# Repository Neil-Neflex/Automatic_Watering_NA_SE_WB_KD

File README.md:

Ce dépôt est organisé de manière à séparer la documentation de conception du code source technique. Pour naviguer efficacement, le projet utilise deux branches distinctes.

## Organisation des branches

- **Branche main**: Centralise la documentation, les rapports de projet et les études d'impact.
- **Branche partie-logicielle**: Contient exclusivement le code source et les fichiers de configuration.

## Contenu de la branche Main

- **DOCS**: Ressources techniques et rapports des membres du groupe par séance.
- **ecoconception**: Analyse du cycle de vie et choix techniques pour minimiser l'empreinte énergétique.
- **Hardware-pcb-eagle**: Schémas électroniques et fichiers PCB réalisés sous Eagle.
- **ProjetS7.pdf**: Présentation S8.
- **RAPPORT.pdf**: Rapport de synthèse présentant les objectifs et résultats du semestre 7 et 8.

## Architecture logicielle

Le code est segmenté par modules fonctionnels(exemple) :
- **Watering_System.ino**: Point d'entrée principal du programme.
- **SensorManagment (.cpp/.h)**: Logique de traitement des capteurs.
- **VanneCase (.h)**: Gestion des états de l'électrovanne.
- **ModuleHorloge (.cpp/.h)**: Gestion du temps réel (RTC).

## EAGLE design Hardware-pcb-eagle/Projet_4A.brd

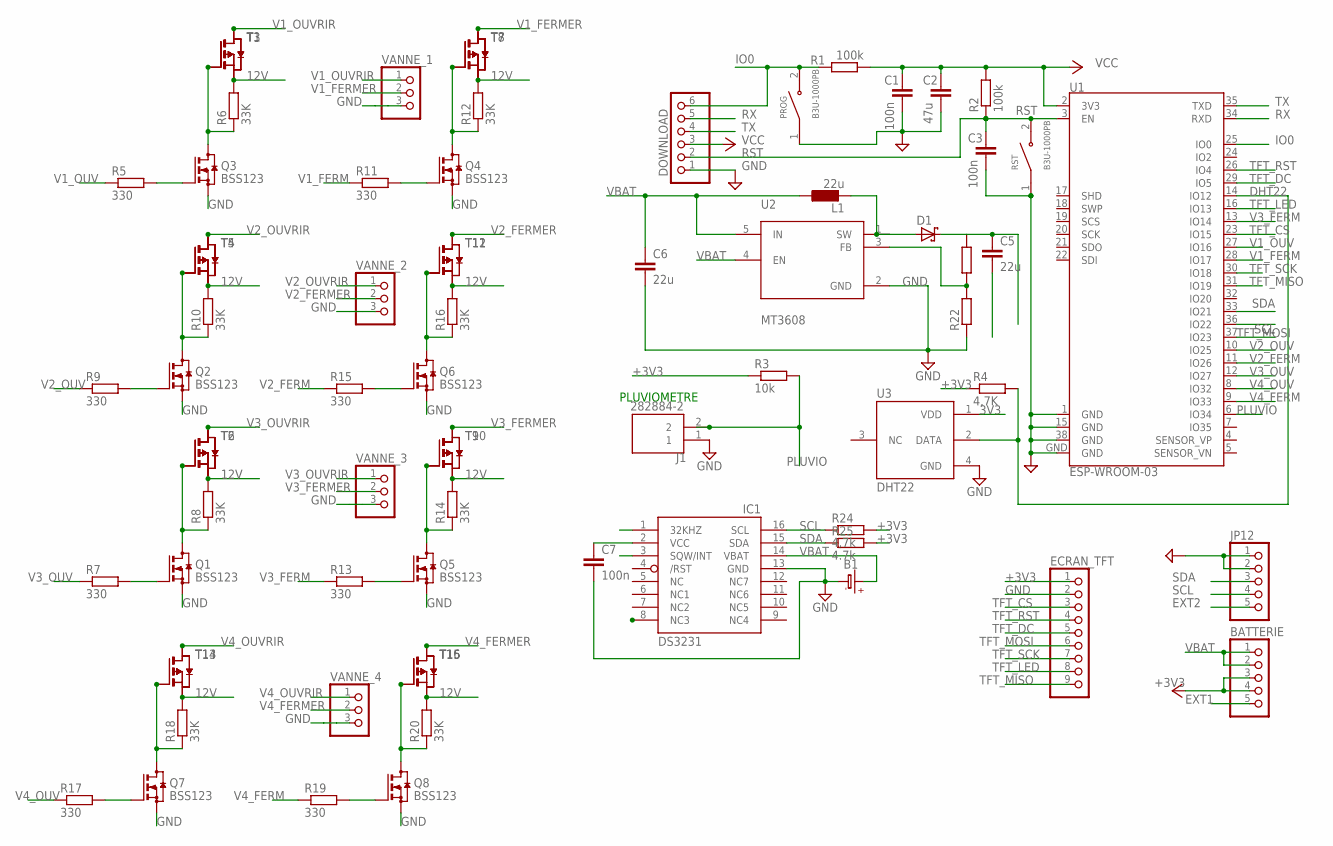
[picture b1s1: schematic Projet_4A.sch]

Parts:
B1: BATTERYCR2032_BAT-HLD-001; CR2032_SMT_BAT-HLD-001
BATTERIE: PINHD-1X5S; 1X05S
C1, C3, C7: 100n; C0805
C2: 47u; C0805
C5, C6: 22u; C0805
D1: SCHOTTKY-DIODEAG; AG
DOWNLOAD: PINHD-1X6S; 1X06S
ECRAN_TFT: PINHD-1X9; 1X09
IC1: DS3231/SO; SO16W
J1: 282884-2; TE_282884-2
JP12: PINHD-1X5S; 1X05S
L1: 22u; 0204/7
PROG: B3U-1000PB; SW_B3U-1000PB
Q1, Q2, Q3, Q4, Q5, Q6, Q7, Q8: BSS123; SOT23
R1, R2: 100k; R1206
R3: 10k; R0805
R4: 4,7K; 0207/10
R5, R7, R9, R11, R13, R15, R17, R19: 330; 0207/10
R6, R8, R10, R12, R14, R16, R18, R20: 33K; 0207/10
R22: R-EU_0204/2V; 0204V
R24: 4,7k; 0204V
R25: 4.7k; 0204V
RST: B3U-1000PB; SW_B3U-1000PB
T1, T2, T3, T4, T5, T6, T7, T8, T9, T10, T11, T12, T13, T14, T15, T16: PMOSSOT23; SOT-23
U1: ESP-WROOM-03
U2: MT3608; SOT95P280X145-6N
U3: DHT22; XDCR_DHT22
VANNE_1, VANNE_2, VANNE_3, VANNE_4: PINHD-1X3; 1X03

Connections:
3V3: U3.1 (VDD)
12V: C5.1, D1.C, R6.2, R8.2, R10.2, R12.2, R14.2, R16.2, R18.2, R20.2, T1.2 (S), T2.2 (S), T3.2 (S), T4.2 (S), T5.2 (S), T6.2 (S), T7.2 (S), T8.2 (S), T9.2 (S), T10.2 (S), T11.2 (S), T12.2 (S), T13.2 (S), T14.2 (S), T15.2 (S), T16.2 (S)
+3V3: BATTERIE.3, BATTERIE.4, C7.1, ECRAN_TFT.1, IC1.2 (VCC), R3.1, R4.1, R24.2, R25.2
+12V: Q3.3 (D), R6.1, T1.3 (G), T3.3 (G)
+12V1: Q2.3 (D), R10.1, T4.3 (G), T5.3 (G)
+12V2: Q1.3 (D), R8.1, T2.3 (G), T6.3 (G)
+12V3: Q4.3 (D), R12.1, T7.3 (G), T8.3 (G)
+12V4: Q5.3 (D), R14.1, T9.3 (G), T10.3 (G)
+12V5: Q6.3 (D), R16.1, T11.3 (G), T12.3 (G)
+12V6: Q7.3 (D), R18.1, T13.3 (G), T14.3 (G)
+12V7: Q8.3 (D), R20.1, T15.3 (G), T16.3 (G)
DHT22: R4.2, U1.14 (IO12), U3.2 (DATA)
EXT1: BATTERIE.5
EXT2: JP12.5
GND: B1.-, C1.2, C2.2, C3.2, C6.2, C7.2, DOWNLOAD.1, ECRAN_TFT.2, IC1.13 (GND), J1.1, JP12.1, JP12.2, PROG.1, Q1.2 (S), Q2.2 (S), Q3.2 (S), Q4.2 (S), Q5.2 (S), Q6.2 (S), Q7.2 (S), Q8.2 (S), R22.1, RST.1, U1.1 (GND), U1.15 (GND), U1.38 (GND), U1.GND, U2.2 (GND), U3.4 (GND), VANNE_1.3, VANNE_2.3, VANNE_3.3, VANNE_4.3
GND1: C5.2
IO0: DOWNLOAD.6, PROG.2, R1.2, U1.25 (IO0)
unnamed: Q3.1 (G), R5.2
unnamed: Q2.1 (G), R9.2
unnamed: Q1.1 (G), R7.2
unnamed: Q4.1 (G), R11.2
unnamed: Q5.1 (G), R13.2
unnamed: Q6.1 (G), R15.2
unnamed: Q7.1 (G), R17.2
unnamed: Q8.1 (G), R19.2
unnamed: D1.A, L1.2, U2.1 (SW)
unnamed: R22.2, U2.3 (FB)
PLUVIO: J1.2, R3.2, U1.6 (IO34)
RST: C3.1, DOWNLOAD.2, R2.1, RST.2, U1.3 (EN)
RX: DOWNLOAD.5, U1.34 (RXD)
SCL: IC1.16 (SCL), JP12.4, R24.1, U1.36 (IO22)
SDA: IC1.15 (SDA), JP12.3, R25.1, U1.33 (IO21)
TFT_CS: ECRAN_TFT.3, U1.23 (IO15)
TFT_DC: ECRAN_TFT.5, U1.29 (IO5)
TFT_LED: ECRAN_TFT.8, U1.16 (IO13)
TFT_MISO: ECRAN_TFT.9, U1.31 (IO19)
TFT_MOSI: ECRAN_TFT.6, U1.37 (IO23)
TFT_RST: ECRAN_TFT.4, U1.26 (IO4)
TFT_SCK: ECRAN_TFT.7, U1.30 (IO18)
TX: DOWNLOAD.4, U1.35 (TXD)
V1_FERM: R11.1, U1.28 (IO17)
V1_FERMER: T7.1 (D), T8.1 (D), VANNE_1.2
V1_OUV: R5.1, U1.27 (IO16)
V1_OUVRIR: T1.1 (D), T3.1 (D), VANNE_1.1
V2_FERM: R15.1, U1.11 (IO26)
V2_FERMER: T11.1 (D), T12.1 (D), VANNE_2.2
V2_OUV: R9.1, U1.10 (IO25)
V2_OUVRIR: T4.1 (D), T5.1 (D), VANNE_2.1
V3_FERM: R13.1, U1.13 (IO14)
V3_FERMER: T9.1 (D), T10.1 (D), VANNE_3.2
V3_OUV: R7.1, U1.12 (IO27)
V3_OUVRIR: T2.1 (D), T6.1 (D), VANNE_3.1
V4_FERM: R19.1, U1.9 (IO33)
V4_FERMER: T15.1 (D), T16.1 (D), VANNE_4.2
V4_OUV: R17.1, U1.8 (IO32)
V4_OUVRIR: T13.1 (D), T14.1 (D), VANNE_4.1
VBAT: B1.+$1 (+), B1.+$2 (+), BATTERIE.1, BATTERIE.2, C6.1, IC1.14 (VBAT), L1.1, U2.4 (EN), U2.5 (IN)
VCC: C1.1, C2.1, DOWNLOAD.3, R1.1, R2.2, U1.2 (3V3)

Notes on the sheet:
PLUVIOMETRE

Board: 2 copper layers, 71 parts (0 on the bottom side), 54 nets, no tracks yet.

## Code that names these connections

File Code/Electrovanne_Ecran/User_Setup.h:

#define TFT_MISO 19
#define TFT_MOSI 23
#define TFT_SCLK 18
#define TFT_CS   15
#define TFT_DC   5
#define TFT_RST  4
#define TFT_BL   13
#define TFT_BACKLIGHT_ON HIGH

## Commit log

2025-10-26 Add technical documentation for irrigation system sensors
2025-10-26 Rapport_semaine1
2025-10-27 Create seance1-2
2025-10-27 Rename seance1-2 to Salma elfiache (seance1-2)
2025-11-09 Add documentation for DHT11 sensor implementation
    Document the implementation and testing of the DHT11 sensor for measuring temperature and humidity in an automatic irrigation system, including installation, wiring, test code, and observations.
2025-11-09 Rapport_seeance3
2025-11-09 Add project report for session 3 on GPIO assignments
    Document the GPIO pin assignments for the ESP32 microcontroller and their respective components, including the LED screen, valves, sensors, and RTC.
2025-11-09 Create salma elfiache _seance3
2025-11-09 Create salmaelfiache_seance3
2025-11-16 Update ndeyekhadyDIOP_seance_3
2025-11-16 Seance 4
    Document the implementation and validation of the DHT22 sensor and the Lexca001 rain gauge integration.
2025-11-16 SEANCE 4
2025-11-16 Rename CR_NeilAmrane_Séance 4.pdf to Neil/CR_NeilAmrane_Séance 4.pdf
2025-11-22 Add documentation on battery management and ULP coprocessor
    Document the study of battery management and ULP coprocessor integration for ESP32.
2025-11-22 Add documentation for battery management and ULP coprocessor
    Document the study of battery management and ULP coprocessor integration for ESP32, including collaborative work on rain gauge sensor integration and energy-saving strategies.
2025-11-22 Enhance documentation on battery management and ULP
    Added details about ULP coprocessor functionality and battery management strategies.
2025-11-22 Rename DOCS/Rapport de projet _ S3.pdf to WissalBellahcen _ Seance3.pdf
2025-11-22 Rename WissalBellahcen _ Seance3.pdf to WissalBellahcen _Seance3.pdf
2025-11-22 Rename WissalBellahcen _Seance3.pdf to DOCS/WissalBellahcen _Seance3.pdf
2025-11-30 Add documentation for ULP rain gauge project
    Document the process of using the ULP coprocessor on ESP32 to count rain gauge pulses, including challenges faced and solutions implemented.
2025-11-30 Seances 5 et 6
    This document details the implementation and testing of the Lexca001 rain gauge and soil moisture sensor for an automatic irrigation system. It includes wiring diagrams, code examples, and calibratio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
2025-12-11 Create salma_elfiache seance4
2025-12-11 Create salma elfiache seance 5 -6
2026-01-04 Add documentation for electronic schematic design
    This document details the electronic schematic design process using Eagle, focusing on power management and component integration for an ESP32-based system.
2026-01-11 Import du code
2026-01-11 Nom du fichier principal modifier
2026-01-11 Mise a jour de tout le projet
    A valider sur HardWare mais normalement ca marche
2026-02-15 Add documentation for electronic schematic design
    Document the design and implementation of the electronic schematic, including power management, sensor interfaces, and user interface.
2026-03-15 Add documentation for ESP32 firmware architecture
    Document the architecture and functionalities of the firmware for the ESP32 microcontroller, including the design approach, optimization techniques, and future development plans.
2026-04-21 Ecoconception
    Added project description and functional unit definition for the automated irrigation station.
2026-04-22 Revise README
    Removed definition of Unité Fonctionnelle (UF) and added a question about the environmental impact of an automated irrigation system.
2026-04-28 Suppression des fichiers obsolètes (Code_principal.ino à ulptool.h)
2026-04-28 Suppression du dossier Code
2026-05-01 Add documentation for 4 sessions
    Document the final development sessions focusing on data acquisition reliability, energy optimization, and hardware design for an autonomous irrigation system.
2026-05-02 Rename Rapport_seance7.pdf to WissalBellahcen_Seance7.pdf
2026-05-11 Presentation
2026-05-12 Partie logicielle du projet
2026-05-12 Code déplacé vers partie-logicielle
2026-05-12 Nettoyage : suppression des dossiers docs et scans de la branche logicielle
2026-05-12 Suppression du dossier data de la branche main
2026-05-12 Suppression de ProjetS7 de la branche logicielle
2026-05-12 Add files via upload
    Ajout d'un guide pour comprendre le git
2026-05-20 Ajout du lien Google Drive pour le projet openLCA Projet_declinaison dans ecoconception/
2026-05-20 Ajout du dossier Hardware-pcb-eagle (schémas PCB Eagle)
2026-05-20 Ajout d'un README.md
